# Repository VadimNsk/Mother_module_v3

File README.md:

# Mother_module_v3
Модуль объединения и распределения (материнский)

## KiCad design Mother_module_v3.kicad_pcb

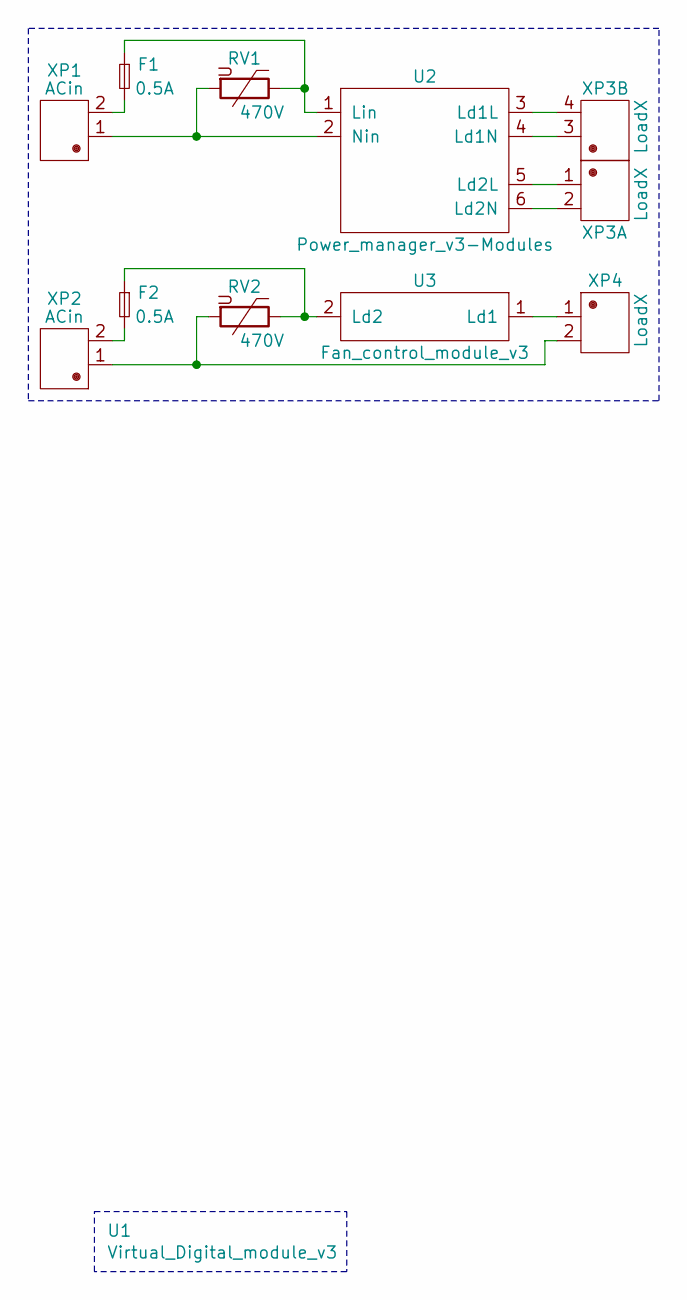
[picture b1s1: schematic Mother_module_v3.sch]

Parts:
F1, F2: 0.5A; FC-05C-E_4x15
RV1, RV2: 470V; RV_Disc_D7mm_W4.5mm_P5mm
U1: Virtual_Digital_module_v3
U2: Power_manager_v3-Modules; Power_manager_v3
U3: Fan_control_module_v3; Fan_controller_v3
XP1, XP2: ACin; XY122R-5.08-02P-14
XP3: LoadX; XY122R-5.08-04P-14
XP4: LoadX; XY122R-5.08-02P-14

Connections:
unnamed: F1.1, RV1.1, U2.1 (Lin)
unnamed: F1.2, XP1.2
unnamed: F2.1, RV2.1, U3.2 (Ld2)
unnamed: F2.2, XP2.2
unnamed: RV1.2, U2.2 (Nin), XP1.1
unnamed: RV2.2, XP2.1, XP4.2
unnamed: U2.3 (Ld1L), XP3.4
unnamed: U2.4 (Ld1N), XP3.3
unnamed: U2.5 (Ld2L), XP3.1
unnamed: U2.6 (Ld2N), XP3.2
unnamed: U3.1 (Ld1), XP4.1

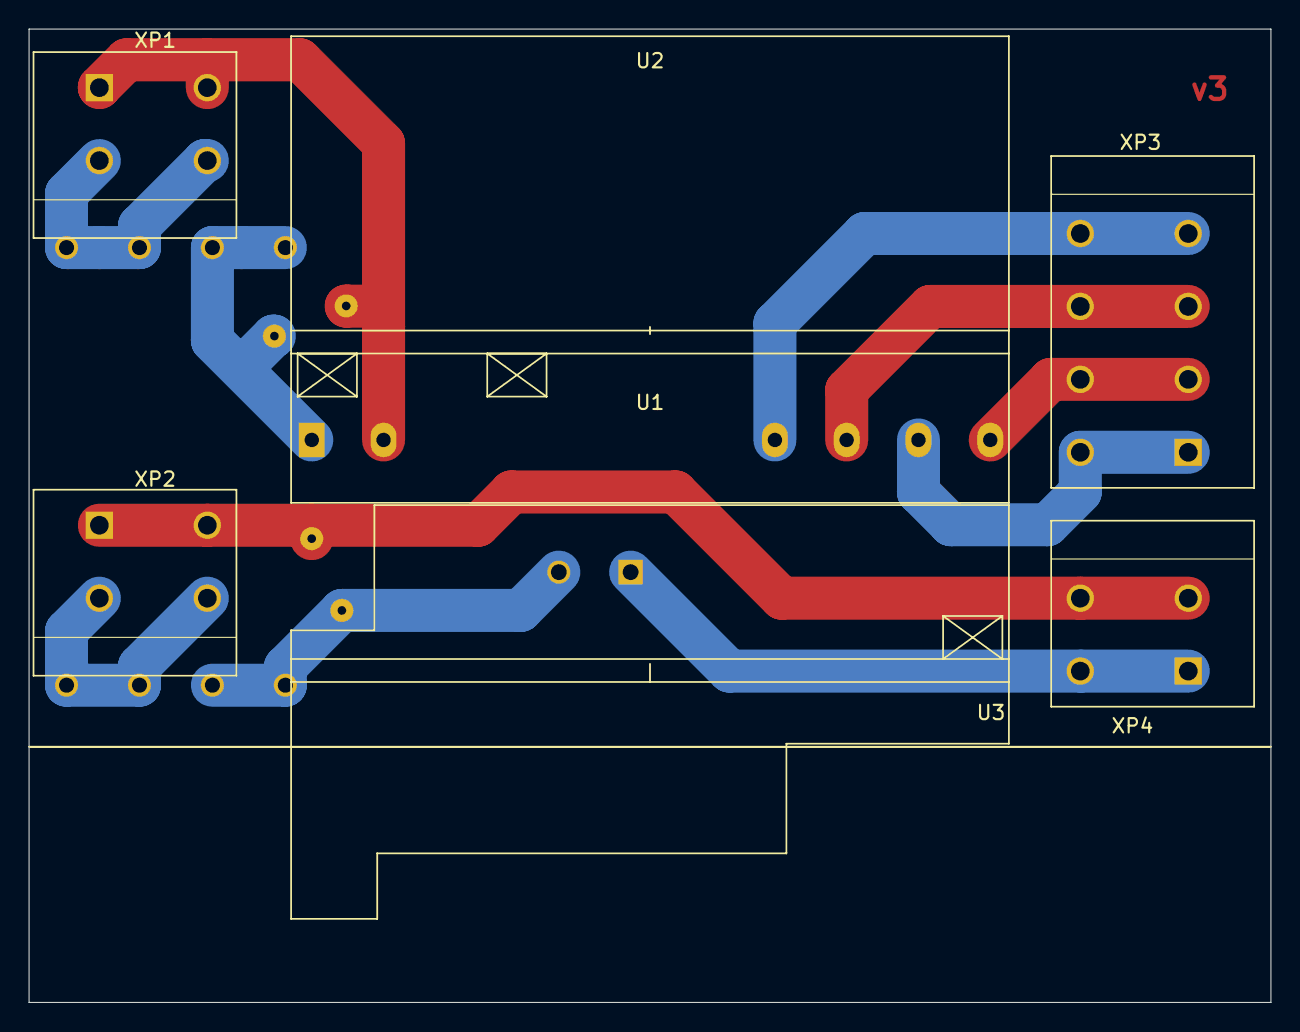
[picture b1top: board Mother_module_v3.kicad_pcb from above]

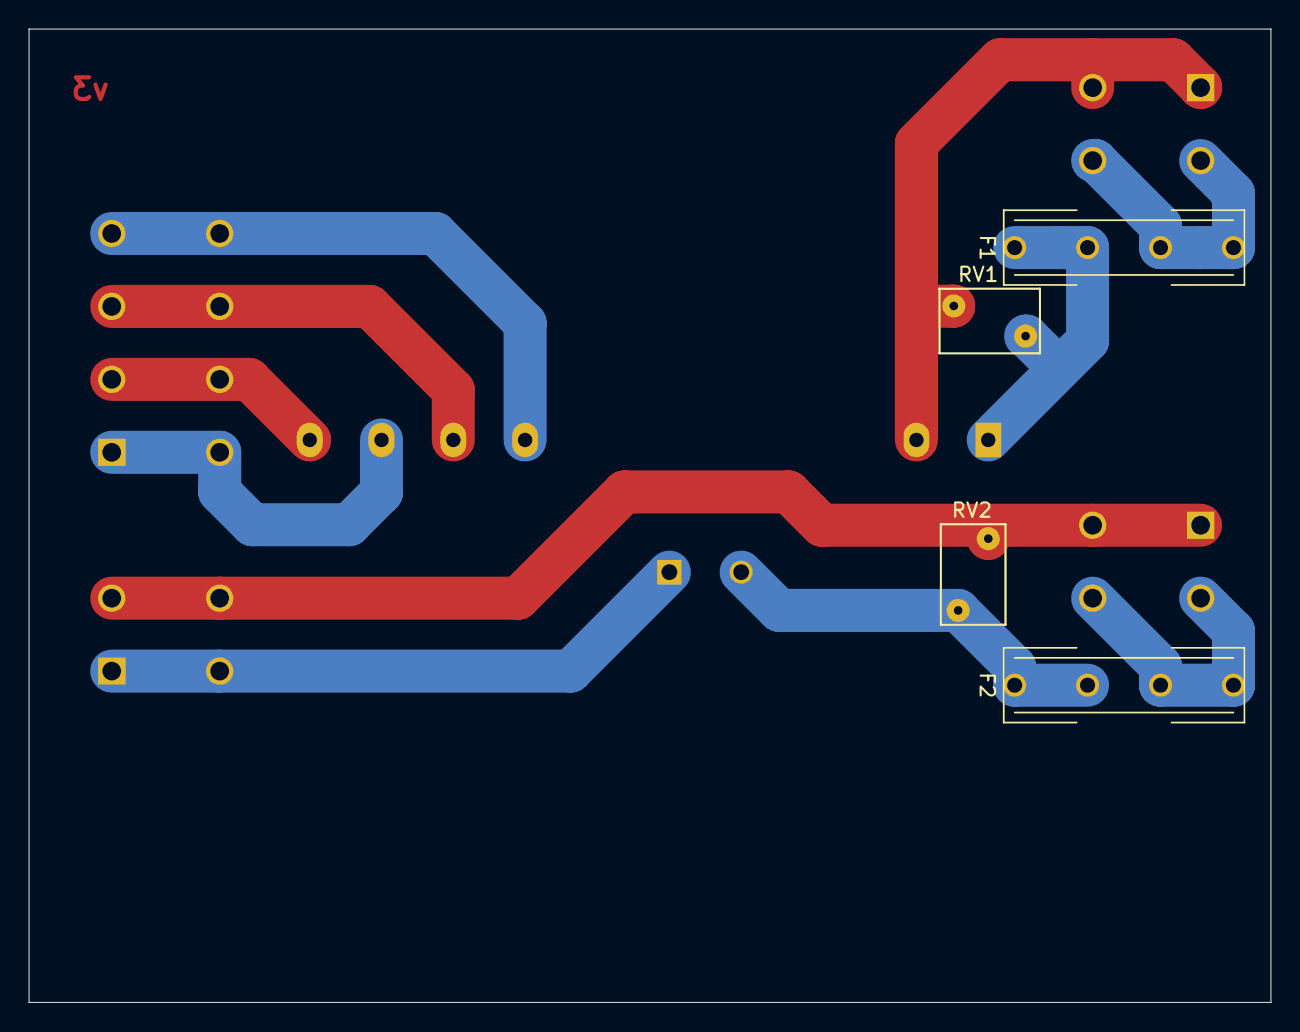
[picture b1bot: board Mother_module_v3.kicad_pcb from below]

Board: 2 copper layers, 86.5 x 67.8 mm, 11 parts (4 on the bottom side), 11 nets.

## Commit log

2021-11-27 Добавлены основные файлы в репозиторий.
2022-01-01 Исправления в схеме и в печатной плате. Размещены два модуля.
2022-01-16 Подправлено положение разъемов и плат модулей.
2022-01-18 Добавлен BOM-файл в HTML-формате, гербера и файлы сверловки
2022-01-18 Delete Mother_module_v3.step
    Файл удаляется ввиду большого размера (больше 100Мб)
2022-01-18 После множества мучений я просто удалил все и заново добавил последние файлы.
2022-01-19 Мелкие правки
2022-02-17 Последние изменения в BOM
